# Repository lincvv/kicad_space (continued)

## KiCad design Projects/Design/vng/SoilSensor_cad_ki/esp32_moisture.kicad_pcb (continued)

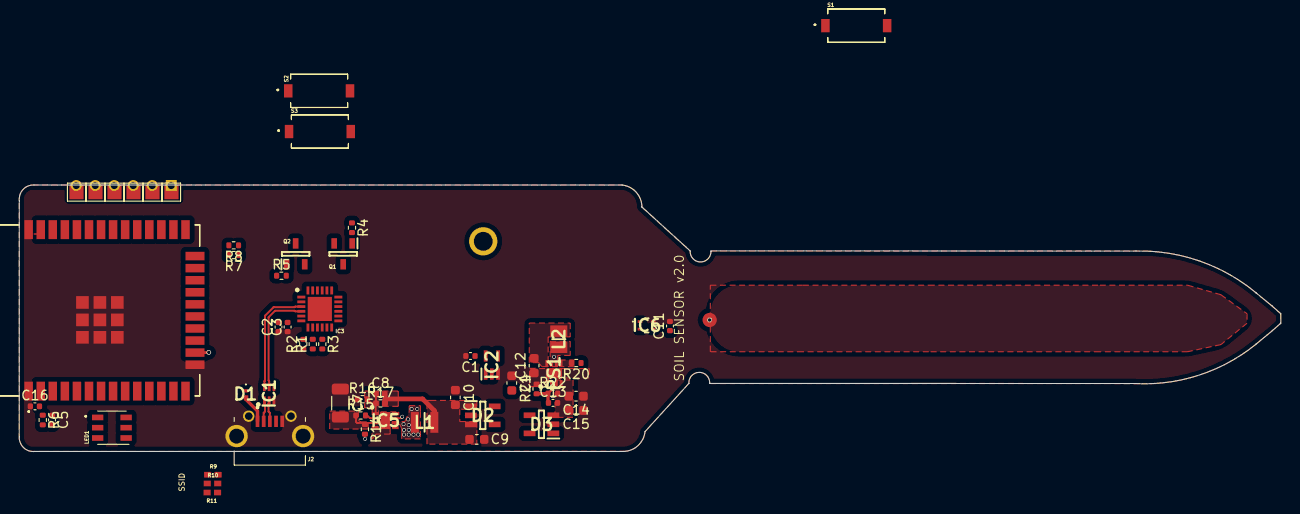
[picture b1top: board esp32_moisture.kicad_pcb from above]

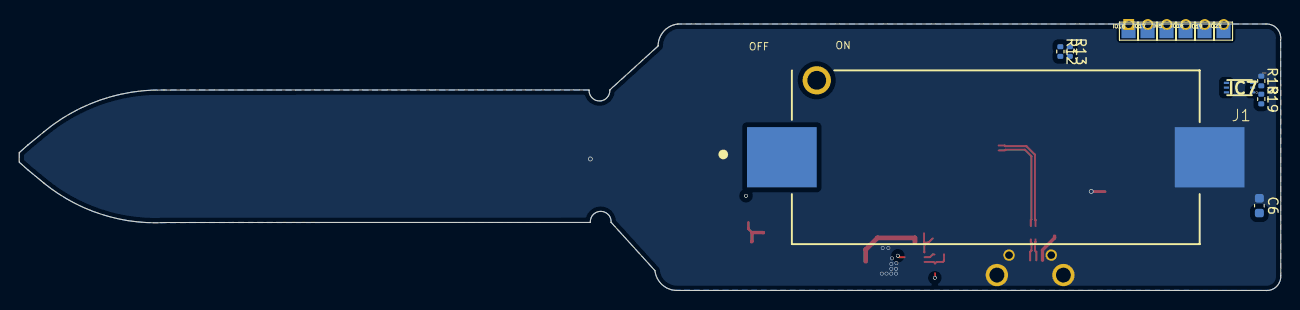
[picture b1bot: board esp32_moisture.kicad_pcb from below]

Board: 4 copper layers, 132.8 x 28.1 mm, 61 parts (7 on the bottom side), 51 nets.

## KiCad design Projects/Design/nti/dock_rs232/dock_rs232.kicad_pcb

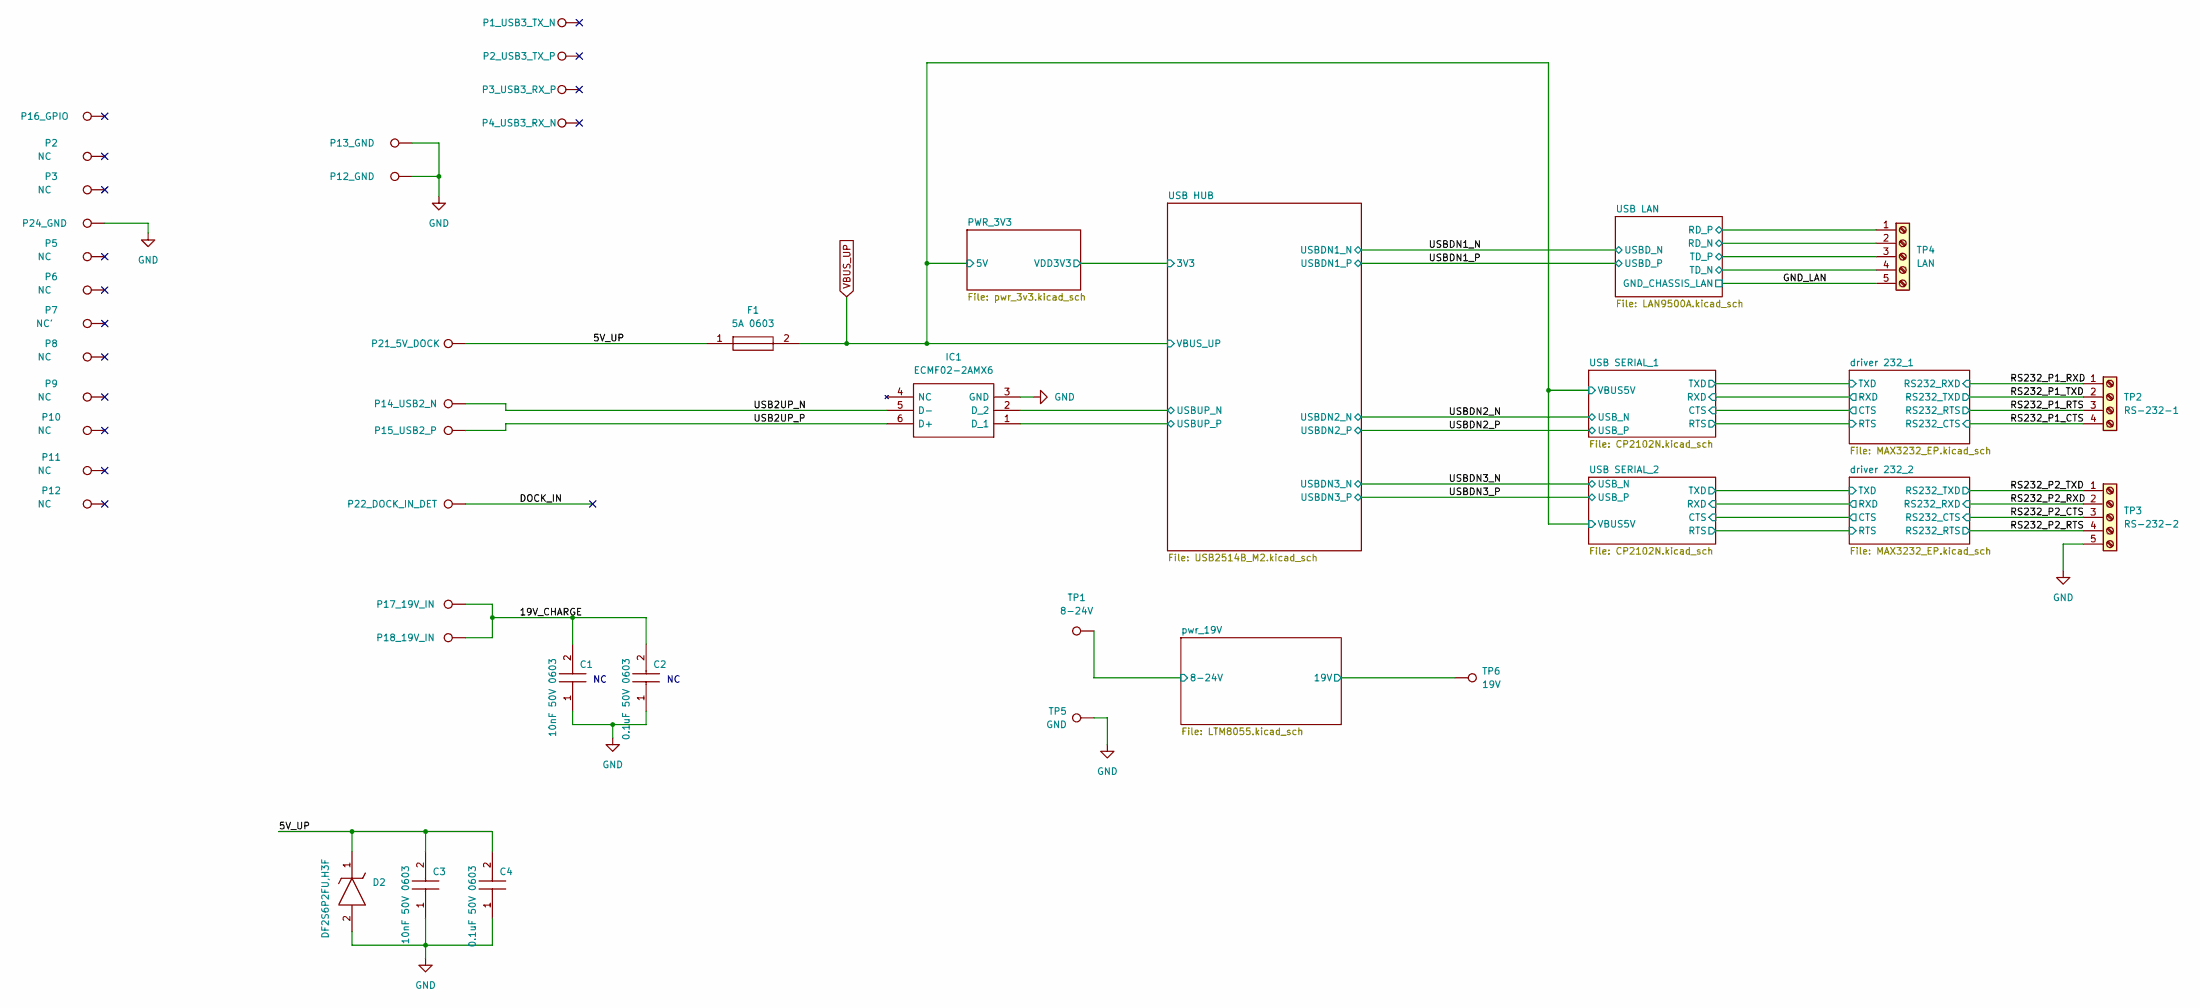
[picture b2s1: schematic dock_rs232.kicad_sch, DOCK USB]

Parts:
C1, C3: 10nF 50V 0603; C_0603_1608Metric; Manufacturer_Part_Number 885012206089; Mouser Part Number 710-885012206089
C2, C4: 0.1uF 50V 0603; C_0603_1608Metric; Manufacturer_Part_Number 06035C104MAT2A; Mouser Part Number 581-06035C104MAT2A
D2: DF2S6P2FU,H3F; SOD2513X115N; Mouser Part Number 757-DF2S6P2FUH3F
F1: 5A 0603; Fuse_0603_1608Metric; Manufacturer_Part_Number 0ABB-5000-TM; Mouser Part Number 530-0ABB-5000-TM
IC1: ECMF02-2AMX6; SON50P150X170X55-6N-D; Manufacturer_Part_Number ECMF02-2AMX6; Mouser Part Number 511-ECMF02-2AMX6
P1: P16_GPIO; TestPoint_THTPad_D1.0mm_Drill0.5mm
P2, P3, P5, P6, P8, P9, P10, P11, P12: NC; TestPoint_THTPad_D1.0mm_Drill0.5mm
P4: P24_GND; TestPoint_THTPad_D1.0mm_Drill0.5mm
P7: NC'; TestPoint_THTPad_D1.0mm_Drill0.5mm
P13: P13_GND; TestPoint_THTPad_D1.0mm_Drill0.5mm
P14: P12_GND; TestPoint_THTPad_D1.0mm_Drill0.5mm
P15: P21_5V_DOCK; TestPoint_THTPad_D1.0mm_Drill0.5mm
P16: P14_USB2_N; TestPoint_THTPad_D1.0mm_Drill0.5mm
P17: P15_USB2_P; TestPoint_THTPad_D1.0mm_Drill0.5mm
P18: P22_DOCK_IN_DET; TestPoint_THTPad_D1.0mm_Drill0.5mm
P19: P17_19V_IN; TestPoint_THTPad_D1.0mm_Drill0.5mm
P20: P18_19V_IN; TestPoint_THTPad_D1.0mm_Drill0.5mm
P21: P1_USB3_TX_N; TestPoint_THTPad_D1.0mm_Drill0.5mm
P22: P2_USB3_TX_P; TestPoint_THTPad_D1.0mm_Drill0.5mm
P23: P3_USB3_RX_P; TestPoint_THTPad_D1.0mm_Drill0.5mm
P24: P4_USB3_RX_N; TestPoint_THTPad_D1.0mm_Drill0.5mm
TP1: 8-24V; TestPoint_THTPad_2.5x2.5mm_Drill1.2mm
TP2: RS-232-1; PinHeader_1x04_P2.54mm_Vertical
TP3: RS-232-2; PinHeader_1x05_P2.54mm_Vertical
TP4: LAN; PinHeader_1x05_P2.00mm_Vertical
TP5: GND; TestPoint_THTPad_2.5x2.5mm_Drill1.2mm
TP6: 19V; TestPoint_THTPad_2.5x2.5mm_Drill1.2mm

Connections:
/5V_UP: C3.2, C4.2, D2.1, F1.1, P15.1
/19V_CHARGE: C1.2, C2.2, P19.1, P20.1
/DOCK_IN: P18.1
/RS232_P1_CTS: TP2.4; also elsewhere on the board
/RS232_P1_RTS: TP2.3; also elsewhere on the board
/RS232_P1_RXD: TP2.1; also elsewhere on the board
/RS232_P1_TXD: TP2.2; also elsewhere on the board
/RS232_P2_CTS: TP3.3; also elsewhere on the board
/RS232_P2_RTS: TP3.4; also elsewhere on the board
/RS232_P2_RXD: TP3.2; also elsewhere on the board
/RS232_P2_TXD: TP3.1; also elsewhere on the board
/USB2UP_N: IC1.5 (D-), P16.1
/USB2UP_P: IC1.6 (D+), P17.1
/USB HUB/USBUP_N: IC1.2 (D_2); also elsewhere on the board
/USB HUB/USBUP_P: IC1.1 (D_1); also elsewhere on the board
/USB LAN/RD_N: TP4.2; also elsewhere on the board
/USB LAN/RD_P: TP4.1; also elsewhere on the board
/USB LAN/TD_N: TP4.4; also elsewhere on the board
/USB LAN/TD_P: TP4.3; also elsewhere on the board
/pwr_19V/8-24V: TP1.1; also elsewhere on the board
/pwr_19V/19V: TP6.1; also elsewhere on the board
GND: C1.1, C2.1, C3.1, C4.1, D2.2, IC1.3 (GND), P4.1, P13.1, P14.1, TP3.5, TP5.1; also elsewhere on the board
GNDPWR: TP4.5; also elsewhere on the board
VBUS_UP: F1.2; also elsewhere on the board

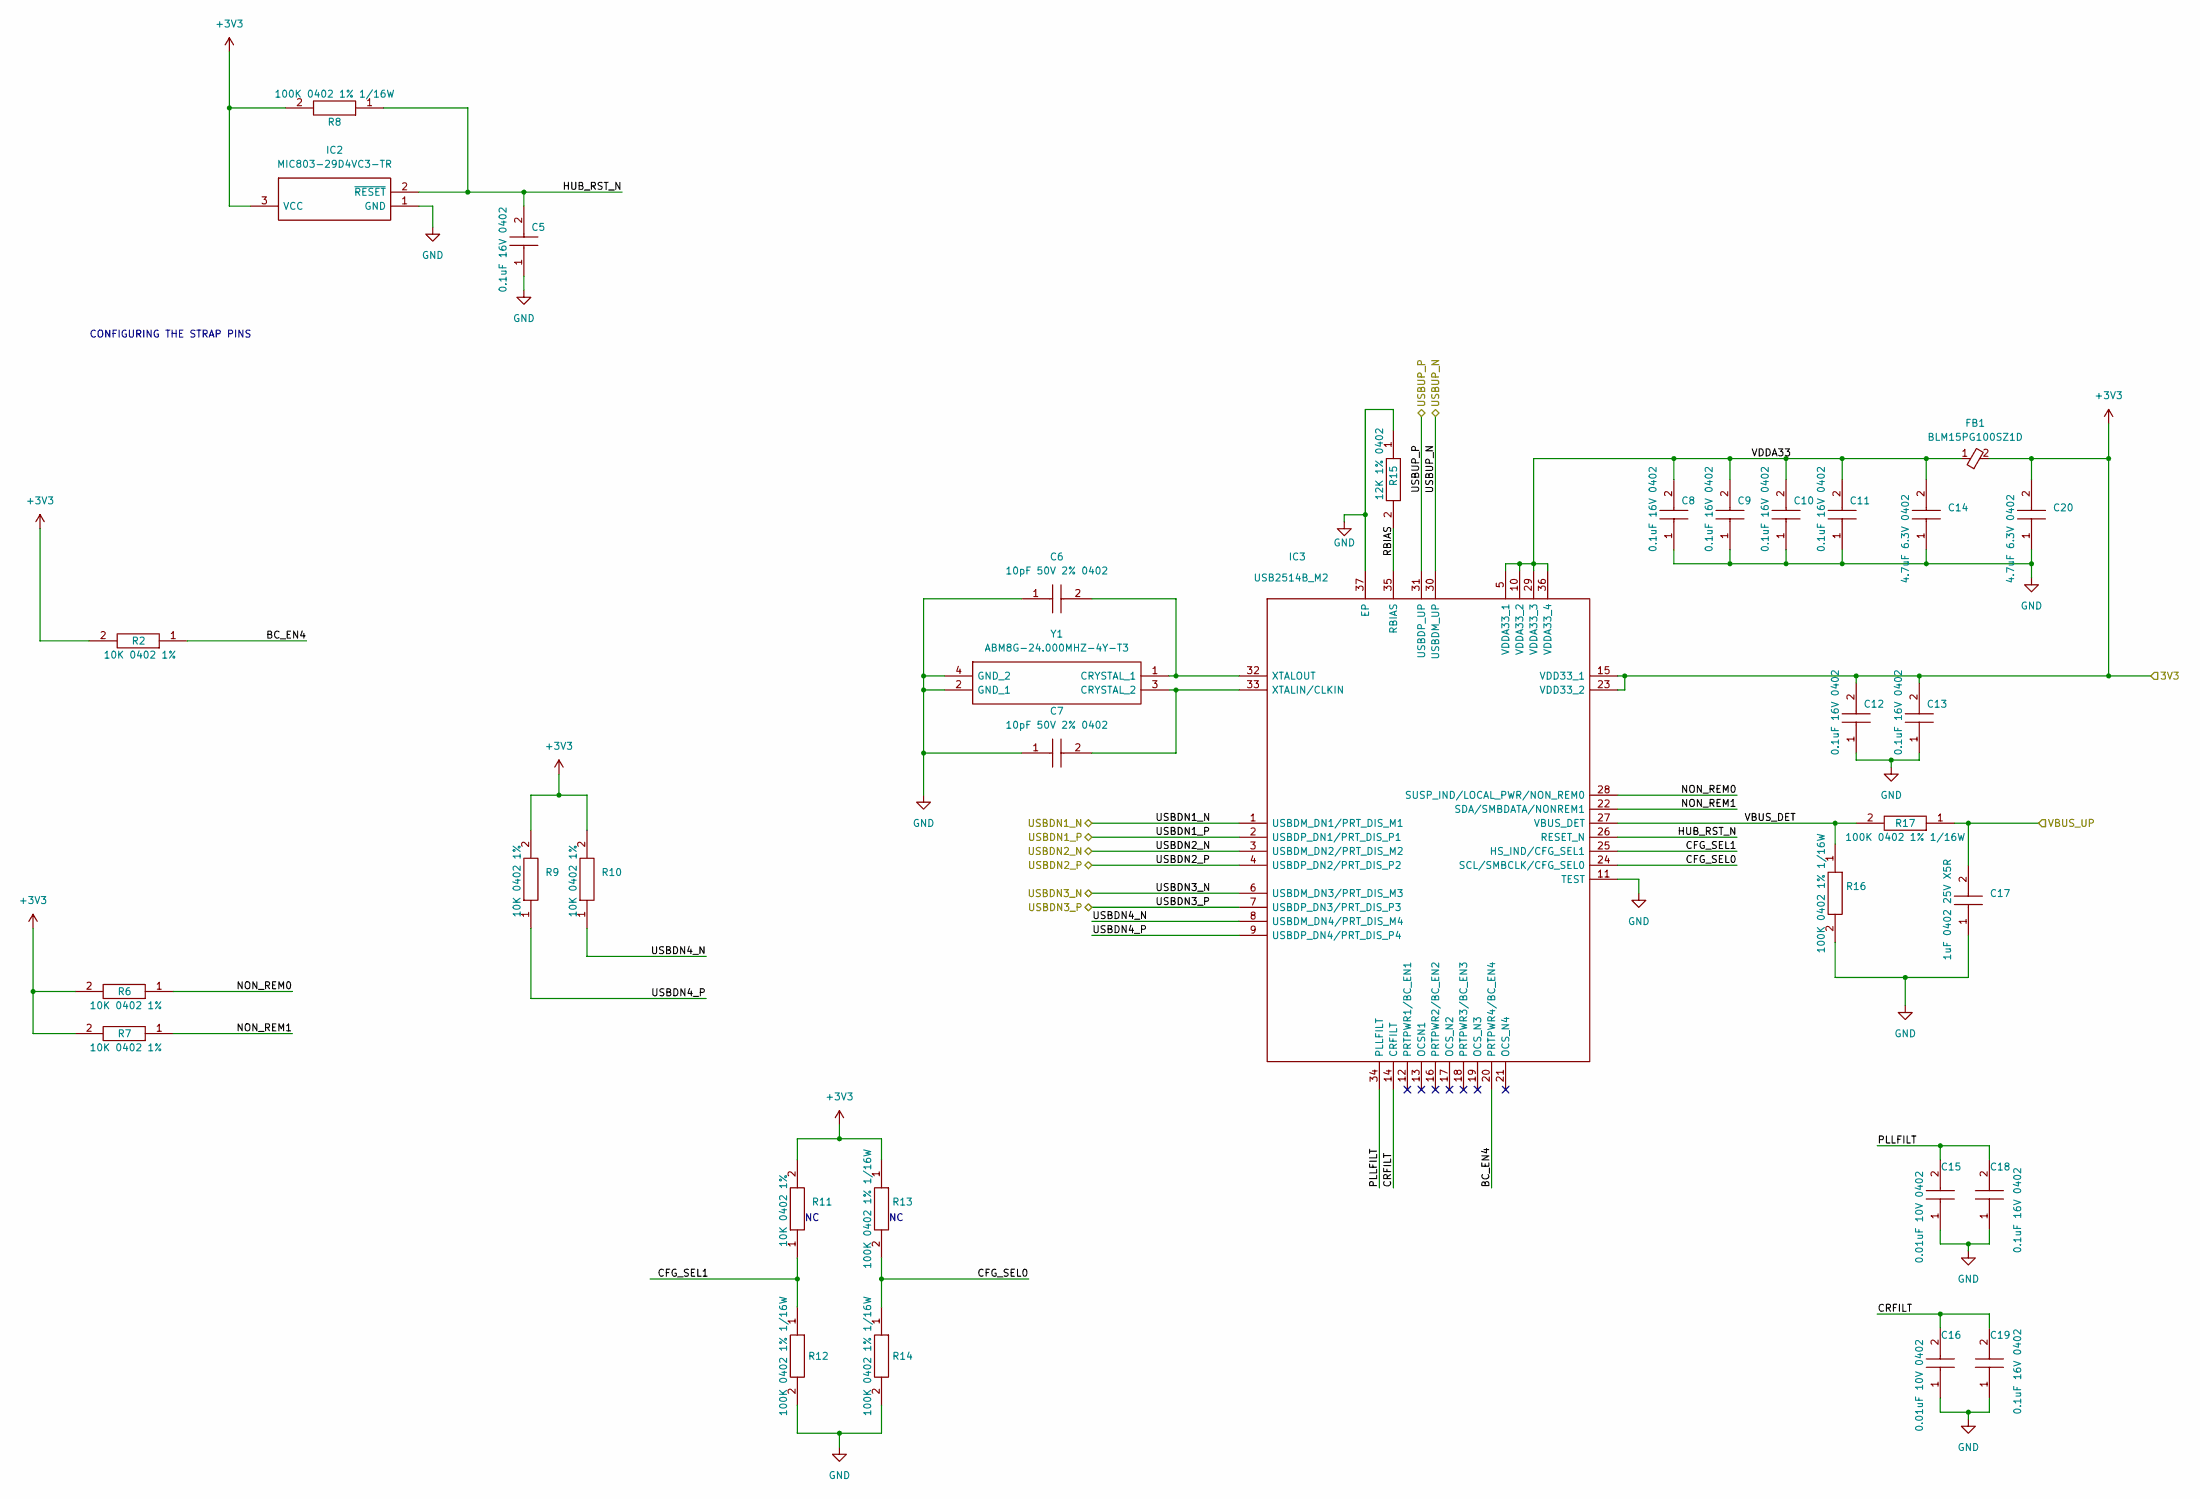
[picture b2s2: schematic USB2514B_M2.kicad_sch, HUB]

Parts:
C5, C8, C9, C10, C11, C12, C13, C18, C19: 0.1uF 16V 0402; C_0402_1005Metric; Manufacturer_Part_Number GRM155R71C104KA88D; Mouser Part Number N/A
C6, C7: 10pF 50V 2% 0402; C_0402_1005Metric; Manufacturer_Part_Number GJM1555C1H100GB01D; Mouser Part Number 81-GJM1555C1H100GB01
C14, C20: 4.7uF 6.3V 0402; C_0402_1005Metric; Manufacturer_Part_Number GRM155R60J475ME47D; Mouser Part Number 81-GRM155R60J475ME7D
C15, C16: 0.01uF 10V 0402; C_0402_1005Metric; Manufacturer_Part_Number 0402ZC103MAT2A; Mouser Part Number 581-0402ZC103MAT2A
C17: 1uF 0402 25V X5R; C_0402_1005Metric; Manufacturer_Part_Number GRM155R61E105KA12D; Mouser Part Number 81-GRM155R61E105KA2D
FB1: BLM15PG100SZ1D; NFZ15SG152SN10B; Manufacturer_Part_Number BLM15PG100SZ1D; Mouser Part Number 81-BLM15PG100SZ1D
IC2: MIC803-29D4VC3-TR; SOT65P210X100-3N; Manufacturer_Part_Number MIC803-29D4VC3-TR; Mouser Part Number 998-MIC803-29D4VC3TR
IC3: USB2514B_M2; QFN50P600X600X100-37N-D; Manufacturer_Part_Number USB2514B/M2; Mouser Part Number 579-USB2514B/M2
R2, R6, R7, R9, R10, R11: 10K 0402 1%; R_0402_1005Metric; Manufacturer_Part_Number AC0402FR-0710KL; Mouser Part Number 603-AC0402FR-0710KL
R8, R12, R13, R14, R16, R17: 100K 0402 1% 1/16W; R_0402_1005Metric; Manufacturer_Part_Number SFR01MZPF1003; Mouser Part Number 755-SFR01MZPF1003
R15: 12K 1% 0402; R_0402_1005Metric; Manufacturer_Part_Number ERJ-U02F1202X
Y1: ABM8G-24.000MHZ-4Y-T3; ABM8G48000MHZ18D2YT; Manufacturer_Part_Number ABM8G-24.000MHZ-4Y-T3; Mouser Part Number 815-ABM8G-24-4YT3

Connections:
+3V3: C12.2, C13.2, C20.2, FB1.2, IC2.3 (VCC), IC3.15 (VDD33_1), IC3.23 (VDD33_2), R2.2, R6.2, R7.2, R8.2, R9.2, R10.2, R11.2, R13.1; also elsewhere on the board
/USB HUB/BC_EN4: IC3.20 (PRTPWR4/BC_EN4), R2.1
/USB HUB/CFG_SEL0: IC3.24 (SCL/SMBCLK/CFG_SEL0), R13.2, R14.1
/USB HUB/CFG_SEL1: IC3.25 (HS_IND/CFG_SEL1), R11.1, R12.1
/USB HUB/CRFILT: C16.2, C19.2, IC3.14 (CRFILT)
/USB HUB/HUB_RST_N: C5.2, IC2.2 (~RESET), IC3.26 (RESET_N), R8.1
/USB HUB/NON_REM0: IC3.28 (SUSP_IND/LOCAL_PWR/NON_REM0), R6.1
/USB HUB/NON_REM1: IC3.22 (SDA/SMBDATA/NONREM1), R7.1
/USB HUB/PLLFILT: C15.2, C18.2, IC3.34 (PLLFILT)
/USB HUB/RBIAS: IC3.35 (RBIAS), R15.2
/USB HUB/USBDN4_N: IC3.8 (USBDM_DN4/PRT_DIS_M4), R10.1
/USB HUB/USBDN4_P: IC3.9 (USBDP_DN4/PRT_DIS_P4), R9.1
/USB HUB/USBUP_N: IC3.30 (USBDM_UP); also elsewhere on the board
/USB HUB/USBUP_P: IC3.31 (USBDP_UP); also elsewhere on the board
/USB HUB/VBUS_DET: IC3.27 (VBUS_DET), R16.1, R17.2
/USB HUB/VDDA33: C8.2, C9.2, C10.2, C11.2, C14.2, FB1.1, IC3.5 (VDDA33_1), IC3.10 (VDDA33_2), IC3.29 (VDDA33_3), IC3.36 (VDDA33_4)
/USBDN1_N: IC3.1 (USBDM_DN1/PRT_DIS_M1); also elsewhere on the board
/USBDN1_P: IC3.2 (USBDP_DN1/PRT_DIS_P1); also elsewhere on the board
/USBDN2_N: IC3.3 (USBDM_DN2/PRT_DIS_M2); also elsewhere on the board
/USBDN2_P: IC3.4 (USBDP_DN2/PRT_DIS_P2); also elsewhere on the board
/USBDN3_N: IC3.6 (USBDM_DN3/PRT_DIS_M3); also elsewhere on the board
/USBDN3_P: IC3.7 (USBDP_DN3/PRT_DIS_P3); also elsewhere on the board
GND: C5.1, C6.1, C7.1, C8.1, C9.1, C10.1, C11.1, C12.1, C13.1, C14.1, C15.1, C16.1, C17.1, C18.1, C19.1, C20.1, IC2.1 (GND), IC3.11 (TEST), IC3.37 (EP), R12.2, R14.2, R15.1, R16.2, Y1.2 (GND_1), Y1.4 (GND_2); also elsewhere on the board
unnamed: C6.2, IC3.32 (XTALOUT), Y1.1 (CRYSTAL_1)
unnamed: C7.2, IC3.33 (XTALIN/CLKIN), Y1.3 (CRYSTAL_2)
VBUS_UP: C17.2, R17.1; also elsewhere on the board

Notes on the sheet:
CONFIGURING THE STRAP PINS

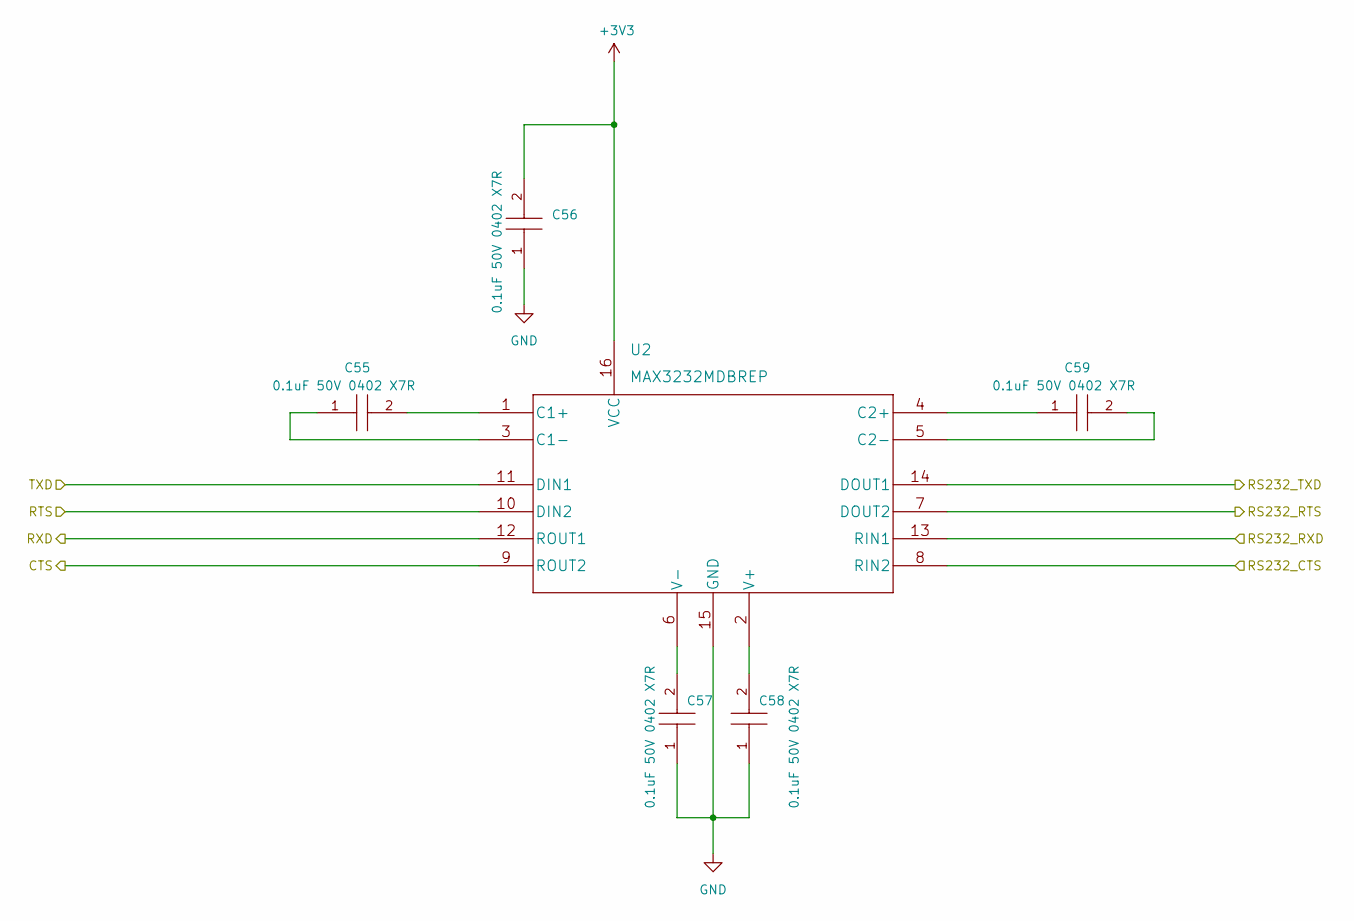
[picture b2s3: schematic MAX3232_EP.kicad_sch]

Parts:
C55, C56, C57, C58, C59: 0.1uF 50V 0402 X7R; C_0402_1005Metric; Manufacturer_Part_Number GRM155R71H104KE14D; Mouser Part Number 81-GRM155R71H104KE4D
U2: MAX3232MDBREP

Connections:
+3V3: C56.2, U2.16 (VCC); also elsewhere on the board
/RS232_P1_CTS: U2.8 (RIN2); also elsewhere on the board
/RS232_P1_RTS: U2.7 (DOUT2); also elsewhere on the board
/RS232_P1_RXD: U2.13 (RIN1); also elsewhere on the board
/RS232_P1_TXD: U2.14 (DOUT1); also elsewhere on the board
/USB SERIAL_1/CTS: U2.9 (ROUT2); also elsewhere on the board
/USB SERIAL_1/RTS: U2.10 (DIN2); also elsewhere on the board
/USB SERIAL_1/RXD: U2.12 (ROUT1); also elsewhere on the board
/USB SERIAL_1/TXD: U2.11 (DIN1); also elsewhere on the board
GND: C56.1, C57.1, C58.1, U2.15 (GND); also elsewhere on the board
unnamed: C55.1, U2.3 (C1-)
unnamed: C55.2, U2.1 (C1+)
unnamed: C57.2, U2.6 (V-)
unnamed: C58.2, U2.2 (V+)
unnamed: C59.1, U2.4 (C2+)
unnamed: C59.2, U2.5 (C2-)

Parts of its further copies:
C29, C30, C31, C32, C33: 0.1uF 50V 0402 X7R; C_0402_1005Metric; Manufacturer_Part_Number GRM155R71H104KE14D; Mouser Part Number 81-GRM155R71H104KE4D
U1: MAX3232MDBREP

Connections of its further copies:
+3V3: C30.2, U1.16 (VCC); also elsewhere on the board
/RS232_P2_CTS: U1.8 (RIN2); also elsewhere on the board
/RS232_P2_RTS: U1.7 (DOUT2); also elsewhere on the board
/RS232_P2_RXD: U1.13 (RIN1); also elsewhere on the board
/RS232_P2_TXD: U1.14 (DOUT1); also elsewhere on the board
/USB SERIAL_2/CTS: U1.9 (ROUT2); also elsewhere on the board
/USB SERIAL_2/RTS: U1.10 (DIN2); also elsewhere on the board
/USB SERIAL_2/RXD: U1.12 (ROUT1); also elsewhere on the board
/USB SERIAL_2/TXD: U1.11 (DIN1); also elsewhere on the board
GND: C30.1, C31.1, C32.1, U1.15 (GND); also elsewhere on the board
unnamed: C29.1, U1.3 (C1-)
unnamed: C29.2, U1.1 (C1+)
unnamed: C31.2, U1.6 (V-)
unnamed: C32.2, U1.2 (V+)
unnamed: C33.1, U1.4 (C2+)
unnamed: C33.2, U1.5 (C2-)

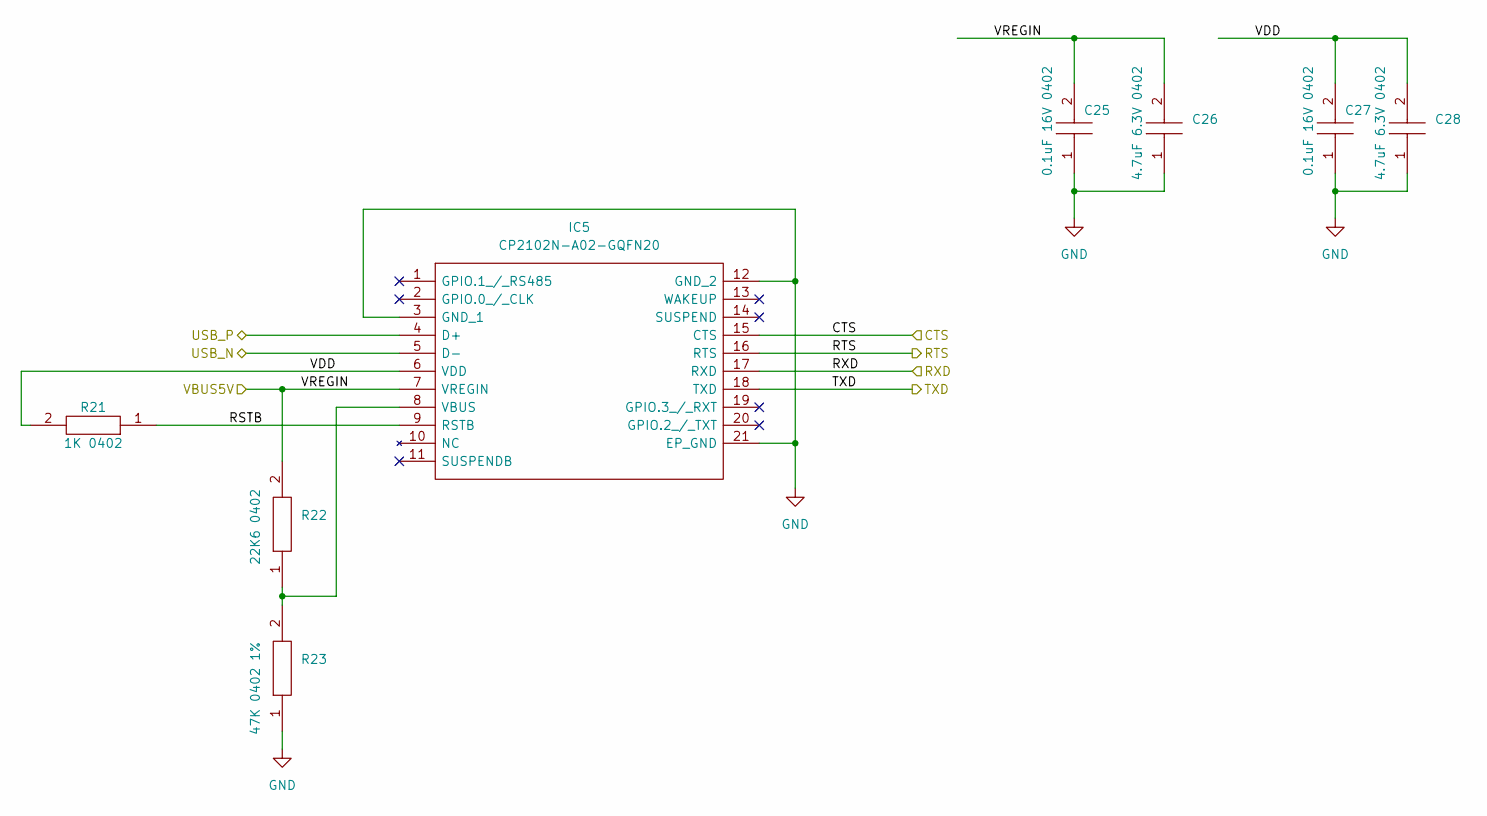
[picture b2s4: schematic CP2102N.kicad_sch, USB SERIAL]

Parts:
C25, C27: 0.1uF 16V 0402; C_0402_1005Metric; Manufacturer_Part_Number GRM155R71C104KA88D; Mouser Part Number N/A
C26, C28: 4.7uF 6.3V 0402; C_0402_1005Metric; Manufacturer_Part_Number GRM155R60J475ME47D; Mouser Part Number 81-GRM155R60J475ME7D
IC5: CP2102N-A02-GQFN20; CP2102NA02GQFN20; Manufacturer_Part_Number CP2102N-A02-GQFN20; Mouser Part Number 634-CP2102NA02GQFN20
R21: 1K 0402; R_0402_1005Metric; Manufacturer_Part_Number RT0402FRE071KL; Mouser Part Number 603-RT0402FRE071KL
R22: 22K6 0402; R_0402_1005Metric; Manufacturer_Part_Number CPF0402B22K6E1; Mouser Part Number 279-CPF0402B22K6E1
R23: 47K 0402 1%; R_0402_1005Metric; Manufacturer_Part_Number AT0402FRE0747KL

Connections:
/USB SERIAL_1/CTS: IC5.15 (CTS); also elsewhere on the board
/USB SERIAL_1/RSTB: IC5.9 (RSTB), R21.1
/USB SERIAL_1/RTS: IC5.16 (RTS); also elsewhere on the board
/USB SERIAL_1/RXD: IC5.17 (RXD); also elsewhere on the board
/USB SERIAL_1/TXD: IC5.18 (TXD); also elsewhere on the board
/USB SERIAL_1/VDD: C27.2, C28.2, IC5.6 (VDD), R21.2
/USBDN2_N: IC5.5 (D-); also elsewhere on the board
/USBDN2_P: IC5.4 (D+); also elsewhere on the board
GND: C25.1, C26.1, C27.1, C28.1, IC5.3 (GND_1), IC5.12 (GND_2), IC5.21 (EP_GND), R23.1; also elsewhere on the board
unnamed: IC5.8 (VBUS), R22.1, R23.2
VBUS_UP: C25.2, C26.2, IC5.7 (VREGIN), R22.2; also elsewhere on the board

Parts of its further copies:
C21, C23: 0.1uF 16V 0402; C_0402_1005Metric; Manufacturer_Part_Number GRM155R71C104KA88D; Mouser Part Number N/A
C22, C24: 4.7uF 6.3V 0402; C_0402_1005Metric; Manufacturer_Part_Number GRM155R60J475ME47D; Mouser Part Number 81-GRM155R60J475ME7D
IC4: CP2102N-A02-GQFN20; CP2102NA02GQFN20; Manufacturer_Part_Number CP2102N-A02-GQFN20; Mouser Part Number 634-CP2102NA02GQFN20
R18: 1K 0402; R_0402_1005Metric; Manufacturer_Part_Number RT0402FRE071KL; Mouser Part Number 603-RT0402FRE071KL
R19: 22K6 0402; R_0402_1005Metric; Manufacturer_Part_Number CPF0402B22K6E1; Mouser Part Number 279-CPF0402B22K6E1
R20: 47K 0402 1%; R_0402_1005Metric; Manufacturer_Part_Number AT0402FRE0747KL

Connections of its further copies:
/USB SERIAL_2/CTS: IC4.15 (CTS); also elsewhere on the board
/USB SERIAL_2/RSTB: IC4.9 (RSTB), R18.1
/USB SERIAL_2/RTS: IC4.16 (RTS); also elsewhere on the board
/USB SERIAL_2/RXD: IC4.17 (RXD); also elsewhere on the board
/USB SERIAL_2/TXD: IC4.18 (TXD); also elsewhere on the board
/USB SERIAL_2/VDD: C23.2, C24.2, IC4.6 (VDD), R18.2
/USBDN3_N: IC4.5 (D-); also elsewhere on the board
/USBDN3_P: IC4.4 (D+); also elsewhere on the board
GND: C21.1, C22.1, C23.1, C24.1, IC4.3 (GND_1), IC4.12 (GND_2), IC4.21 (EP_GND), R20.1; also elsewhere on the board
unnamed: IC4.8 (VBUS), R19.1, R20.2
VBUS_UP: C21.2, C22.2, IC4.7 (VREGIN), R19.2; also elsewhere on the board

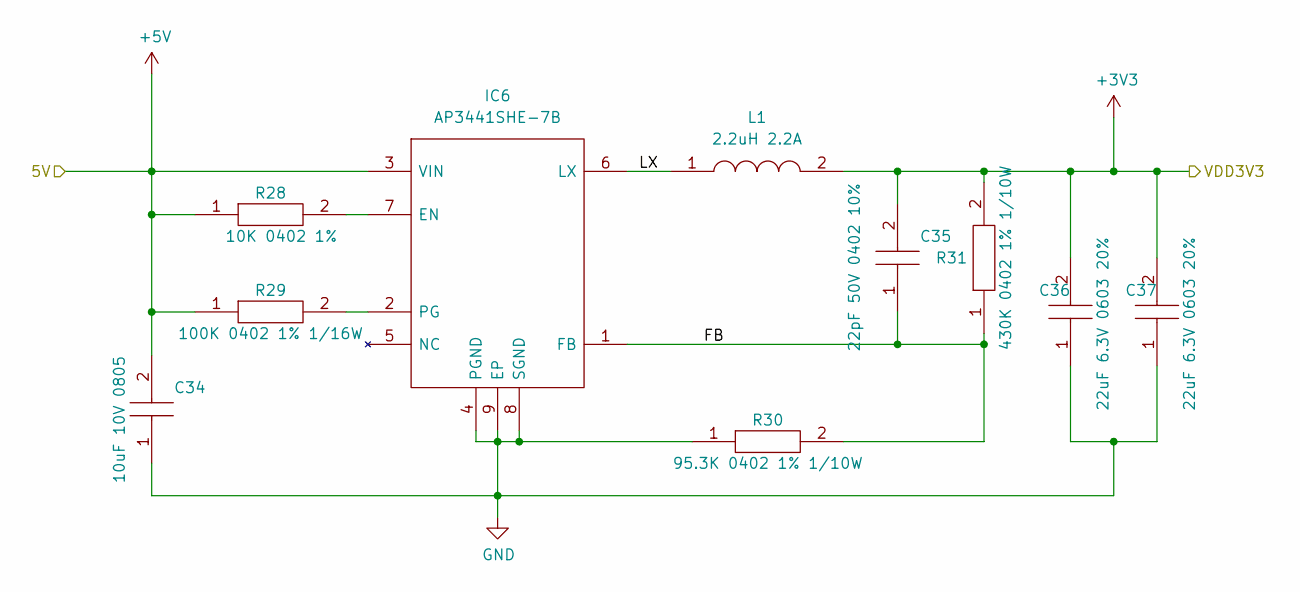
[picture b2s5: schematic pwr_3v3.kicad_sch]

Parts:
C34: 10uF 10V 0805; C_0805_2012Metric; Manufacturer_Part_Number LMK212ABJ106KG8T; Mouser Part Number 963-LMK212ABJ106KG8T
C35: 22pF 50V 0402 10%; C_0402_1005Metric; Manufacturer_Part_Number C0402C220K5RACTU; Mouser Part Number 80-C0402C220K5RACTU
C36, C37: 22uF 6.3V 0603 20%; C_0603_1608Metric; Manufacturer_Part_Number GRM188R60J226MEA0D; Mouser Part Number 81-GRM188R60J226ME0D
IC6: AP3441SHE-7B; SON50P201X201X60-9N-D; Manufacturer_Part_Number AP3441SHE-7B; Mouser Part Number 621-AP3441SHE-7B
L1: 2.2uH 2.2A; DFE2HCAH1R0MJ0L; Manufacturer_Part_Number 1239AS-H-2R2M=P2; Mouser Part Number 81-1239AS-H-2R2MP2
R28: 10K 0402 1%; R_0402_1005Metric; Manufacturer_Part_Number AC0402FR-0710KL; Mouser Part Number 603-AC0402FR-0710KL
R29: 100K 0402 1% 1/16W; R_0402_1005Metric; Manufacturer_Part_Number SFR01MZPF1003; Mouser Part Number 755-SFR01MZPF1003
R30: 95.3K 0402 1% 1/10W; R_0402_1005Metric; Manufacturer_Part_Number ERJ-U02F9532X; Mouser Part Number 667-ERJ-U02F9532X
R31: 430K 0402 1% 1/10W; R_0402_1005Metric; Manufacturer_Part_Number ERJ-U02F4303X

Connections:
+3V3: C35.2, C36.2, C37.2, L1.2, R31.2; also elsewhere on the board
/PWR_3V3/FB: C35.1, IC6.1 (FB), R30.2, R31.1
/PWR_3V3/LX: IC6.6 (LX), L1.1
GND: C34.1, C36.1, C37.1, IC6.4 (PGND), IC6.8 (SGND), IC6.9 (EP), R30.1; also elsewhere on the board
unnamed: IC6.2 (PG), R29.2
unnamed: IC6.7 (EN), R28.2
VBUS_UP: C34.2, IC6.3 (VIN), R28.1, R29.1; also elsewhere on the board

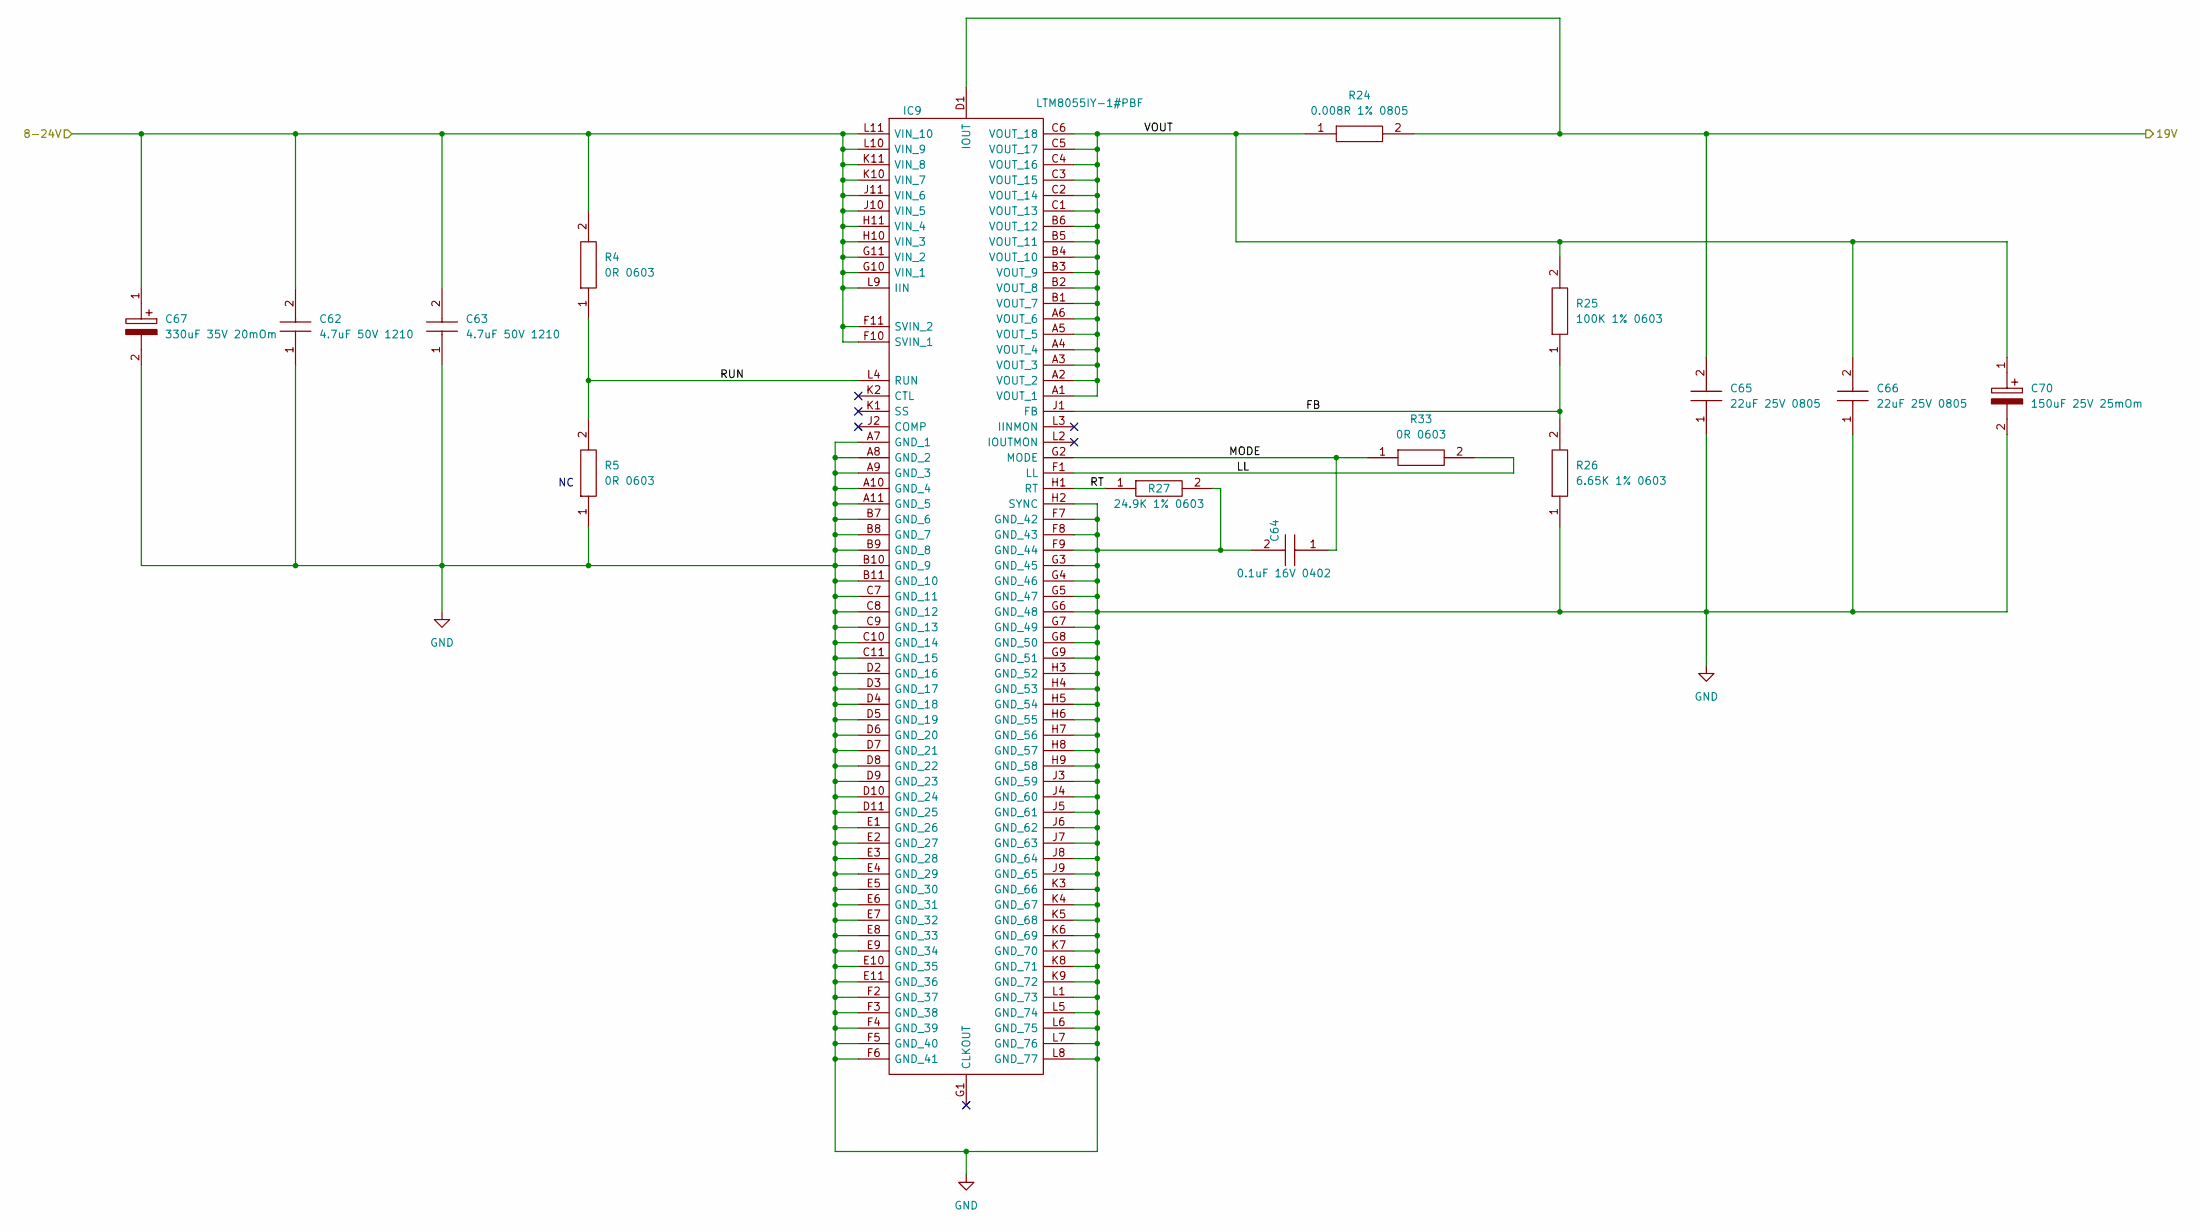
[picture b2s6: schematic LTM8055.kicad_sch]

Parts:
C62, C63: 4.7uF 50V 1210; C_1210_3225Metric; Manufacturer_Part_Number CC1210KFX7R9BB475; Mouser Part Number 603-CC1210KFX7R9B475
C64: 0.1uF 16V 0402; C_0402_1005Metric; Manufacturer_Part_Number GRM155R71C104KA88D; Mouser Part Number N/A
C65, C66: 22uF 25V 0805; C_0805_2012Metric; Manufacturer_Part_Number GRT21BR61E226ME13L; Mouser Part Number 81-GRT21BR61E226ME3L
C67: 330uF 35V 20mOm; CAPPRD530W65D1000H1050; Manufacturer_Part_Number EEH-AZK1V331B; Mouser Part Number 667-EEH-AZK1V331B
C70: 150uF 25V 25mOm; CAPAE1030X800N; Mouser Part Number 661-APXG250A151MJ80G
IC9: LTM8055IY-1#PBF; BGA121C127P11X11_1500X1500X512; Manufacturer_Part_Number LTM8055IY-1#PBF; Mouser Part Number 584-LTM8055IY-1#PBF
R4, R5, R33: 0R 0603; R_0603_1608Metric; Manufacturer_Part_Number ERJ-U030R00V; Mouser Part Number 667-ERJ-U030R00V
R24: 0.008R 1% 0805; RESC2012X47N; Manufacturer_Part_Number PMR10EZPFU8L00; Mouser Part Number 755-PMR10EZPFU8L00
R25: 100K 1% 0603; R_0603_1608Metric; Manufacturer_Part_Number ERJ-PA3F1003V; Mouser Part Number 667-ERJ-PA3F1003V
R26: 6.65K 1% 0603; R_0603_1608Metric; Manufacturer_Part_Number ERJ-PA3F6651V
R27: 24.9K 1% 0603; R_0603_1608Metric; Manufacturer_Part_Number CR0603-FX-2492ELF; Mouser Part Number 652-CR0603FX-2492ELF

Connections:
/pwr_19V/8-24V: C62.2, C63.2, C67.1, IC9.F10 (SVIN_1), IC9.F11 (SVIN_2), IC9.G10 (VIN_1), IC9.G11 (VIN_2), IC9.H10 (VIN_3), IC9.H11 (VIN_4), IC9.J10 (VIN_5), IC9.J11 (VIN_6), IC9.K10 (VIN_7), IC9.K11 (VIN_8), IC9.L9 (IIN), IC9.L10 (VIN_9), IC9.L11 (VIN_10), R4.2; also elsewhere on the board
/pwr_19V/19V: C65.2, IC9.D1 (IOUT), R24.2; also elsewhere on the board
/pwr_19V/FB: IC9.J1 (FB), R25.1, R26.2
/pwr_19V/LL: IC9.F1 (LL), R33.2
/pwr_19V/MODE: C64.1, IC9.G2 (MODE), R33.1
/pwr_19V/RT: IC9.H1 (RT), R27.1
/pwr_19V/RUN: IC9.L4 (RUN), R4.1, R5.2
/pwr_19V/VOUT: C66.2, C70.1, IC9.A1 (VOUT_1), IC9.A2 (VOUT_2), IC9.A3 (VOUT_3), IC9.A4 (VOUT_4), IC9.A5 (VOUT_5), IC9.A6 (VOUT_6), IC9.B1 (VOUT_7), IC9.B2 (VOUT_8), IC9.B3 (VOUT_9), IC9.B4 (VOUT_10), IC9.B5 (VOUT_11), IC9.B6 (VOUT_12), IC9.C1 (VOUT_13), IC9.C2 (VOUT_14), IC9.C3 (VOUT_15), IC9.C4 (VOUT_16), IC9.C5 (VOUT_17), IC9.C6 (VOUT_18), R24.1, R25.2
GND: C62.1, C63.1, C64.2, C65.1, C66.1, C67.2, C70.2, IC9.A7 (GND_1), IC9.A8 (GND_2), IC9.A9 (GND_3), IC9.A10 (GND_4), IC9.A11 (GND_5), IC9.B7 (GND_6), IC9.B8 (GND_7), IC9.B9 (GND_8), IC9.B10 (GND_9), IC9.B11 (GND_10), IC9.C7 (GND_11), IC9.C8 (GND_12), IC9.C9 (GND_13), IC9.C10 (GND_14), IC9.C11 (GND_15), IC9.D2 (GND_16), IC9.D3 (GND_17), IC9.D4 (GND_18), IC9.D5 (GND_19), IC9.D6 (GND_20), IC9.D7 (GND_21), IC9.D8 (GND_22), IC9.D9 (GND_23), IC9.D10 (GND_24), IC9.D11 (GND_25), IC9.E1 (GND_26), IC9.E2 (GND_27), IC9.E3 (GND_28), IC9.E4 (GND_29), IC9.E5 (GND_30), IC9.E6 (GND_31), IC9.E7 (GND_32), IC9.E8 (GND_33), IC9.E9 (GND_34), IC9.E10 (GND_35), IC9.E11 (GND_36), IC9.F2 (GND_37), IC9.F3 (GND_38), IC9.F4 (GND_39), IC9.F5 (GND_40), IC9.F6 (GND_41), IC9.F7 (GND_42), IC9.F8 (GND_43), IC9.F9 (GND_44), IC9.G3 (GND_45), IC9.G4 (GND_46), IC9.G5 (GND_47), IC9.G6 (GND_48), IC9.G7 (GND_49), IC9.G8 (GND_50), IC9.G9 (GND_51), IC9.H2 (SYNC), IC9.H3 (GND_52), IC9.H4 (GND_53), IC9.H5 (GND_54), IC9.H6 (GND_55), IC9.H7 (GND_56), IC9.H8 (GND_57), IC9.H9 (GND_58), IC9.J3 (GND_59), IC9.J4 (GND_60), IC9.J5 (GND_61), IC9.J6 (GND_62), IC9.J7 (GND_63), IC9.J8 (GND_64), IC9.J9 (GND_65), IC9.K3 (GND_66), IC9.K4 (GND_67), IC9.K5 (GND_68), IC9.K6 (GND_69), IC9.K7 (GND_70), IC9.K8 (GND_71), IC9.K9 (GND_72), IC9.L1 (GND_73), IC9.L5 (GND_74), IC9.L6 (GND_75), IC9.L7 (GND_76), IC9.L8 (GND_77), R5.1, R26.1, R27.2; also elsewhere on the board
